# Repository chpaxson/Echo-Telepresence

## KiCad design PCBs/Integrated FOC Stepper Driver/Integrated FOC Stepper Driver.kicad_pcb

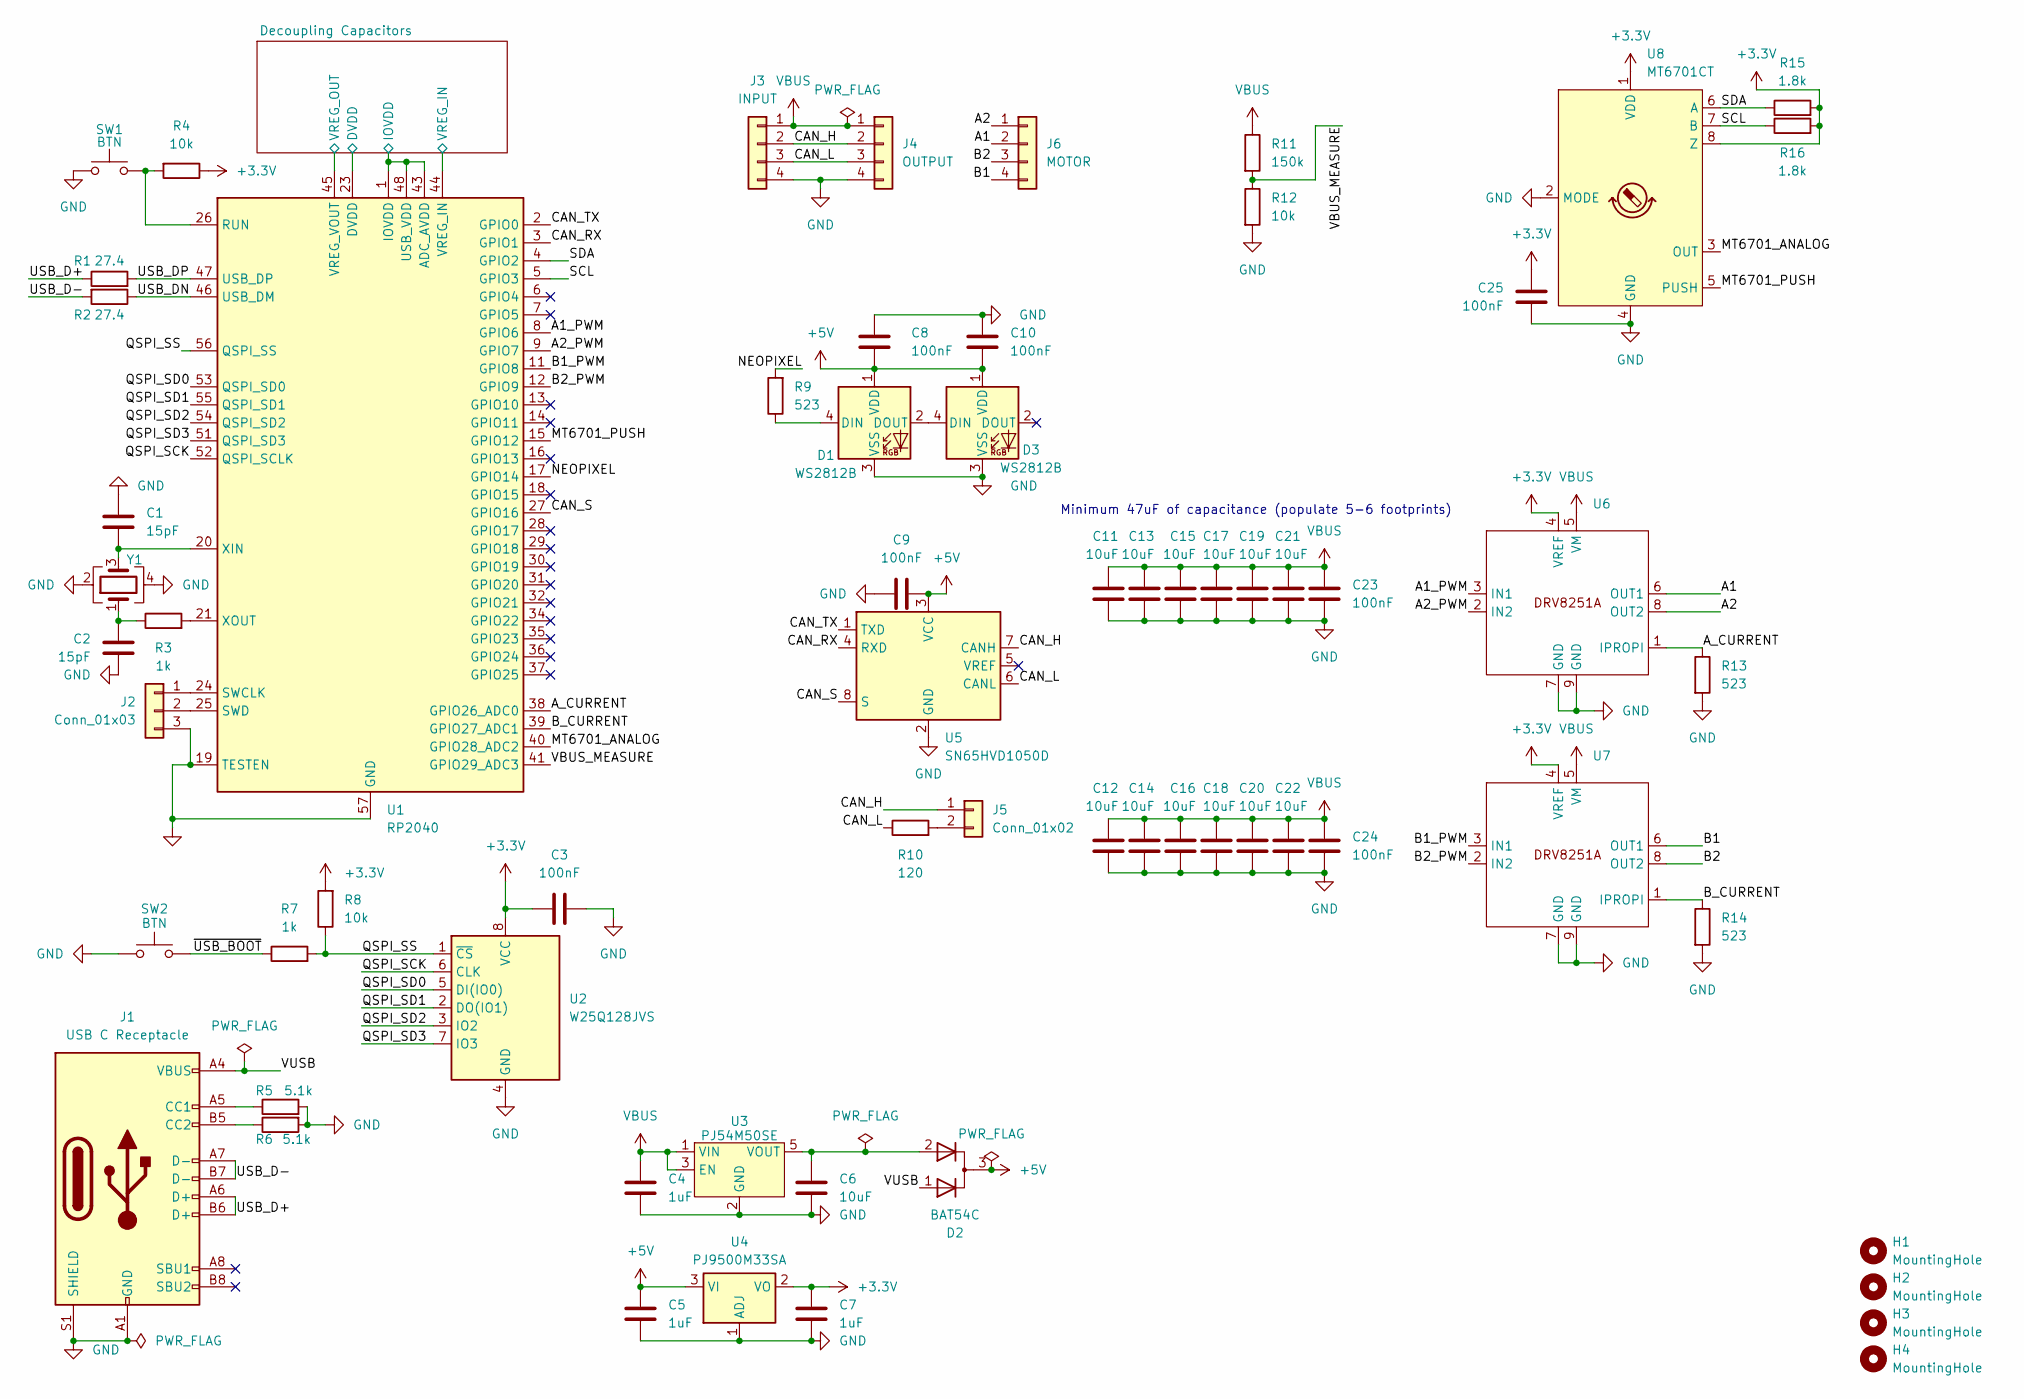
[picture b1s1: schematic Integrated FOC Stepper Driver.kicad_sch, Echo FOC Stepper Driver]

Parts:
C1, C2: 15pF; C_0402_1005Metric; LCSC C18164617
C3, C8, C9, C10, C23, C24: 100nF; C_0402_1005Metric; LCSC C960916
C4, C5, C7: 1uF; C_0402_1005Metric; LCSC C1518208
C6: 10uF; C_0603_1608Metric; LCSC C96446
C11, C12, C13, C14, C15, C16, C17, C18, C19, C20, C21, C22: 10uF; C_0805_2012Metric; LCSC C440198
C25: 100nF; C_0603_1608Metric; LCSC C1591
D1, D3: WS2812B; LED_WS2812B_PLCC4_5.0x5.0mm_P3.2mm
D2: BAT54C; SOT-23; LCSC C37704
H1, H2, H3, H4: MountingHole; MountingHole_3.2mm_M3_DIN965_Pad
J1: USB C Receptacle; USB_C_Receptacle_G-Switch_GT-USB-7010ASV; LCSC C2988369
J2: Conn_01x03; PinHeader_1x03_P2.54mm_Vertical
J3: INPUT; JST_PH_S4B-PH-K_1x04_P2.00mm_Horizontal; LCSC C157926
J4: OUTPUT; JST_PH_S4B-PH-K_1x04_P2.00mm_Horizontal; LCSC C157926
J5: Conn_01x02; PinHeader_1x02_P2.54mm_Vertical
J6: MOTOR; JST_XH_S4B-XH-A_1x04_P2.50mm_Horizontal; LCSC C157925
R1, R2: 27.4; R_0402_1005Metric; LCSC C274349
R3, R7: 1k; R_0402_1005Metric; LCSC C105637
R4, R8, R12: 10k; R_0402_1005Metric; LCSC C60490
R5, R6: 5.1k; R_0402_1005Metric; LCSC C105872
R9, R13, R14: 523; R_0402_1005Metric; LCSC C517803
R10: 120; R_0402_1005Metric; LCSC C114758
R11: 150k; R_0402_1005Metric; LCSC C93947
R15, R16: 1.8k; R_0402_1005Metric; LCSC C163481
SW1, SW2: BTN; SW_SPST_B3U-1000P; LCSC C231329
U1: RP2040; QFN-56-1EP_7x7mm_P0.4mm_EP3.2x3.2mm; LCSC C2040
U2: W25Q128JVS; SOIC-8_5.23x5.23mm_P1.27mm; LCSC C97521
U3: PJ54M50SE; SOT-23-5; LCSC C41784039
U4: PJ9500M33SA; SOT-23; LCSC C20618178
U5: SN65HVD1050D; SOIC-8_3.9x4.9mm_P1.27mm; LCSC C14019
U6, U7: Texas_HSOP-8-1EP_3.9x4.9mm_P1.27mm_ThermalVias; LCSC C5218844
U8: MT6701CT; SO-8_3.9x4.9mm_P1.27mm; LCSC C19711153
Y1: ABM8-272-T3; Crystal_SMD_3225-4Pin_3.2x2.5mm; LCSC C20625731

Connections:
+1V1: U1.23 (DVDD), U1.45 (VREG_VOUT), U1.50 (DVDD); also elsewhere on the board
+3.3V: C3.1, C7.1, C25.1, R4.1, R8.2, R15.2, R16.2, U1.1 (IOVDD), U1.10 (IOVDD), U1.22 (IOVDD), U1.33 (IOVDD), U1.42 (IOVDD), U1.43 (ADC_AVDD), U1.44 (VREG_IN), U1.48 (USB_VDD), U1.49 (IOVDD), U2.8 (VCC), U4.2 (VO), U6.4 (VREF), U7.4 (VREF), U8.1 (VDD), U8.8 (Z); also elsewhere on the board
+5V: C5.1, C8.1, C9.1, C10.1, D1.1 (VDD), D2.3 (K), D3.1 (VDD), U4.3 (VI), U5.3 (VCC)
/A1: J6.2, U6.6 (OUT1)
/A1_PWM: U1.8 (GPIO6), U6.3 (IN1)
/A2: J6.1, U6.8 (OUT2)
/A2_PWM: U1.9 (GPIO7), U6.2 (IN2)
/A_CURRENT: R13.1, U1.38 (GPIO26_ADC0), U6.1 (IPROPI)
/B1: J6.4, U7.6 (OUT1)
/B1_PWM: U1.11 (GPIO8), U7.3 (IN1)
/B2: J6.3, U7.8 (OUT2)
/B2_PWM: U1.12 (GPIO9), U7.2 (IN2)
/B_CURRENT: R14.1, U1.39 (GPIO27_ADC1), U7.1 (IPROPI)
/CAN_H: J3.2, J4.2, J5.1, U5.7 (CANH)
/CAN_L: J3.3, J4.3, R10.1, U5.6 (CANL)
/CAN_RX: U1.3 (GPIO1), U5.4 (RXD)
/CAN_S: U1.27 (GPIO16), U5.8 (S)
/CAN_TX: U1.2 (GPIO0), U5.1 (TXD)
/MT6701_ANALOG: U1.40 (GPIO28_ADC2), U8.3 (OUT)
/MT6701_PUSH: U1.15 (GPIO12), U8.5 (PUSH)
/NEOPIXEL: R9.2, U1.17 (GPIO14)
/QSPI_SCK: U1.52 (QSPI_SCLK), U2.6 (CLK)
/QSPI_SD0: U1.53 (QSPI_SD0), U2.5 (DI(IO0))
/QSPI_SD1: U1.55 (QSPI_SD1), U2.2 (DO(IO1))
/QSPI_SD2: U1.54 (QSPI_SD2), U2.3 (IO2)
/QSPI_SD3: U1.51 (QSPI_SD3), U2.7 (IO3)
/QSPI_SS: R7.2, R8.1, U1.56 (QSPI_SS), U2.1 (~CS)
/SCL: R16.1, U1.5 (GPIO3), U8.7 (B)
/SDA: R15.1, U1.4 (GPIO2), U8.6 (A)
/USB_D+: J1.A6 (D+), J1.B6 (D+), R1.1
/USB_D-: J1.A7 (D-), J1.B7 (D-), R2.2
/USB_DN: R2.1, U1.46 (USB_DM)
/USB_DP: R1.2, U1.47 (USB_DP)
/VBUS_MEASURE: R11.2, R12.1, U1.41 (GPIO29_ADC3)
/VUSB: D2.1 (A), J1.A4 (VBUS), J1.A9 (VBUS), J1.B4 (VBUS), J1.B9 (VBUS)
/~USB_BOOT: R7.1, SW2.2
GND: C1.2, C2.1, C3.2, C4.2, C5.2, C6.2, C7.2, C8.2, C9.2, C10.2, C11.2, C12.2, C13.2, C14.2, C15.2, C16.2, C17.2, C18.2, C19.2, C20.2, C21.2, C22.2, C23.2, C24.2, C25.2, D1.3 (VSS), D3.3 (VSS), J1.A1 (GND), J1.A12 (GND), J1.B1 (GND), J1.B12 (GND), J1.S1 (SHIELD), J2.3, J3.4, J4.4, R5.2, R6.2, R12.2, R13.2, R14.2, SW1.2, SW2.1, U1.19 (TESTEN), U1.57 (GND), U2.4 (GND), U3.2 (GND), U4.1 (ADJ), U5.2 (GND), U6.7 (GND), U6.9 (GND), U7.7 (GND), U7.9 (GND), U8.2 (MODE), U8.4 (GND), Y1.2, Y1.4; also elsewhere on the board
unnamed: C2.2, R3.1, Y1.1
unnamed: D1.4 (DIN), R9.1
unnamed: D1.2 (DOUT), D3.4 (DIN)
unnamed: J1.A5 (CC1), R5.1
unnamed: J1.B5 (CC2), R6.1
unnamed: J2.1, U1.24 (SWCLK)
unnamed: J2.2, U1.25 (SWD)
unnamed: J5.2, R10.2
unnamed: R4.2, SW1.1, U1.26 (RUN)
unnamed: C1.1, U1.20 (XIN), Y1.3
unnamed: R3.2, U1.21 (XOUT)
unnamed: C6.1, D2.2 (A), U3.5 (VOUT)
VBUS: C4.1, C11.1, C12.1, C13.1, C14.1, C15.1, C16.1, C17.1, C18.1, C19.1, C20.1, C21.1, C22.1, C23.1, C24.1, J3.1, J4.1, R11.1, U3.1 (VIN), U3.3 (EN), U6.5 (VM), U7.5 (VM)

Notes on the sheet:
Minimum 47uF of capacitance (populate 5-6 footprints)

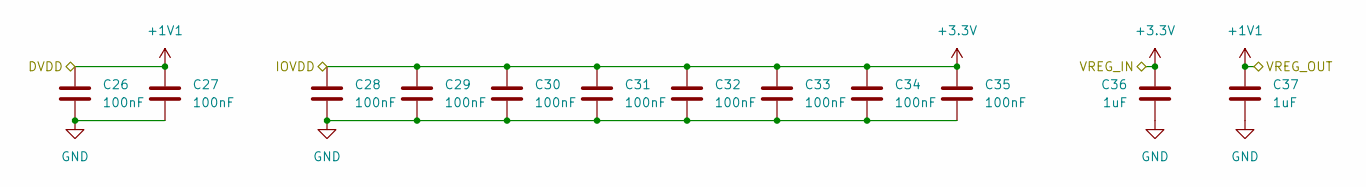
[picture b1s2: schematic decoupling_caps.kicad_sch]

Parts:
C26, C27, C28, C29, C30, C31, C32, C33, C34, C35: 100nF; C_0402_1005Metric; LCSC C960916
C36, C37: 1uF; C_0402_1005Metric; LCSC C1518208

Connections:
+1V1: C26.1, C27.1, C37.1; also elsewhere on the board
+3.3V: C28.1, C29.1, C30.1, C31.1, C32.1, C33.1, C34.1, C35.1, C36.1; also elsewhere on the board
GND: C26.2, C27.2, C28.2, C29.2, C30.2, C31.2, C32.2, C33.2, C34.2, C35.2, C36.2, C37.2; also elsewhere on the board

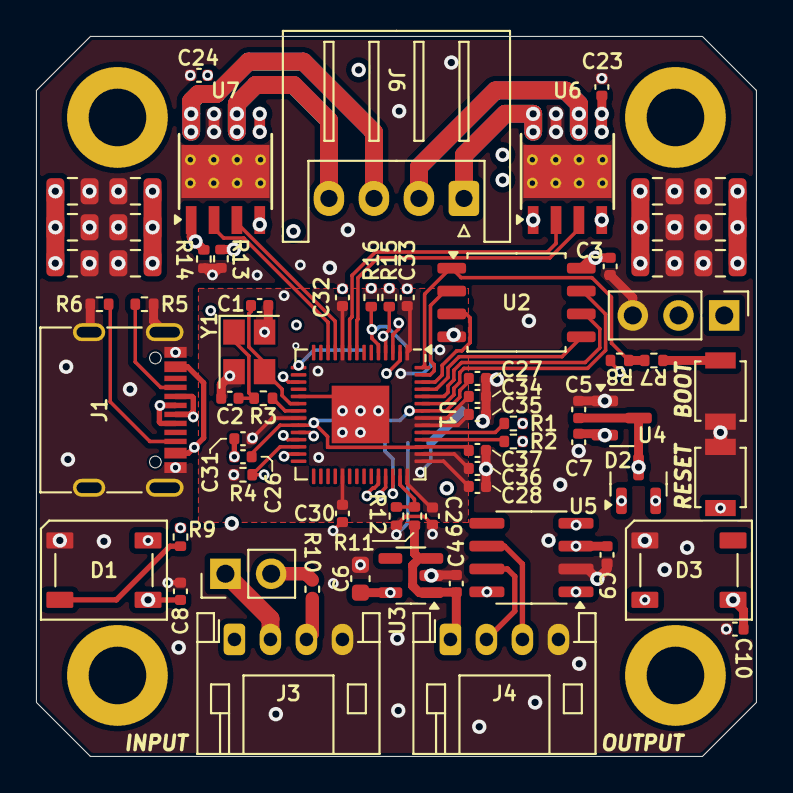
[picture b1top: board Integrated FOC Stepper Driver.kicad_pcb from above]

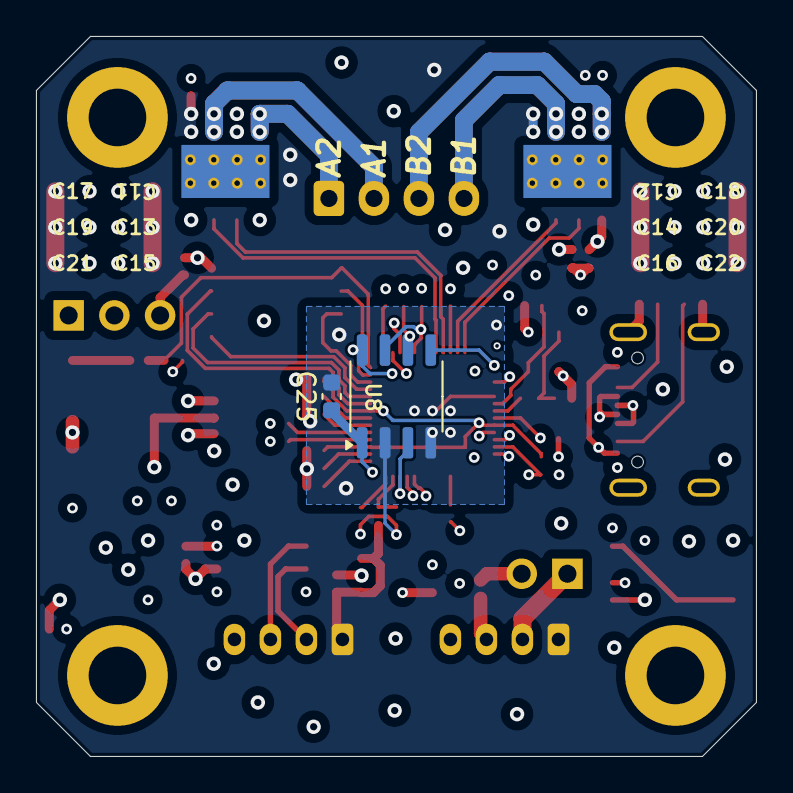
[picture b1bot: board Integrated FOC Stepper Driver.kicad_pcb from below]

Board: 6 copper layers, 40.0 x 40.0 mm, 77 parts (2 on the bottom side), 50 nets.

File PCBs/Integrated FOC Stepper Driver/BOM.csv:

"C1, C2",15pF,~,Capacitor_SMD:C_0402_1005Metric,2,C18164617
"C3, C8-C10, C23, C24, C26-C35",100nF,~,Capacitor_SMD:C_0402_1005Metric,16,C960916
"C4, C5, C7, C36, C37",1uF,~,Capacitor_SMD:C_0402_1005Metric,5,C1518208
C6,10uF,~,Capacitor_SMD:C_0603_1608Metric,1,C96446
C11-C22,10uF,~,Capacitor_SMD:C_0805_2012Metric,12,C440198
C25,100nF,~,Capacitor_SMD:C_0603_1608Metric,1,C1591
D2,BAT54C,~,Package_TO_SOT_SMD:SOT-23,1,C37704
J1,USB C Receptacle,https://www.usb.org/sites/default/files/documents/usb_type-c.zip,Connector_USB:USB_C_Receptacle_G-Switch_GT-USB-7010ASV,1,C2988369
J3,INPUT,~,Connector_JST:JST_PH_S4B-PH-K_1x04_P2.00mm_Horizontal,1,C157926
J4,OUTPUT,~,Connector_JST:JST_PH_S4B-PH-K_1x04_P2.00mm_Horizontal,1,C157926
J6,MOTOR,~,Connector_JST:JST_XH_S4B-XH-A_1x04_P2.50mm_Horizontal,1,C157925
"R1, R2",27.4,~,Resistor_SMD:R_0402_1005Metric,2,C274349
"R3, R7",1k,~,Resistor_SMD:R_0402_1005Metric,2,C105637
"R4, R8, R12",10k,~,Resistor_SMD:R_0402_1005Metric,3,C60490
"R5, R6",5.1k,~,Resistor_SMD:R_0402_1005Metric,2,C105872
"R9, R13, R14",523,~,Resistor_SMD:R_0402_1005Metric,3,C517803
R10,120,~,Resistor_SMD:R_0402_1005Metric,1,C114758
R11,150k,~,Resistor_SMD:R_0402_1005Metric,1,C93947
"R15, R16",1.8k,~,Resistor_SMD:R_0402_1005Metric,2,C163481
"SW1, SW2",BTN,~,Button_Switch_SMD:SW_SPST_B3U-1000P,2,C231329
U1,RP2040,https://datasheets.raspberrypi.com/rp2040/rp2040-datasheet.pdf,Package_DFN_QFN:QFN-56-1EP_7x7mm_P0.4mm_EP3.2x3.2mm,1,C2040
U2,W25Q128JVS,https://www.winbond.com/resource-files/w25q128jv_dtr%20revc%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,Package_SO:SOIC-8_5.23x5.23mm_P1.27mm,1,C97521
U3,PJ54M50SE,,Package_TO_SOT_SMD:SOT-23-5,1,C41784039
U4,PJ9500M33SA,,Package_TO_SOT_SMD:SOT-23,1,C20618178
U5,SN65HVD1050D,http://www.ti.com/lit/ds/symlink/sn65hvd1050.pdf,Package_SO:SOIC-8_3.9x4.9mm_P1.27mm,1,C14019
"U6, U7",~,,Package_SO:Texas_HSOP-8-1EP_3.9x4.9mm_P1.27mm_ThermalVias,2,C5218844
U8,MT6701CT,https://www.magntek.com.cn/upload/MT6701_Rev.1.5.pdf,Package_SO:SO-8_3.9x4.9mm_P1.27mm,1,C19711153
Y1,ABM8-272-T3,~,Crystal:Crystal_SMD_3225-4Pin_3.2x2.5mm,1,C20625731

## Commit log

2025-02-01 PCB Project File Initialization
2025-02-01 Create symbol+footprint libraries for DRV8301, begin refining DRV8301 symbol
2025-02-01 Finish DRV8301 symbol, start implementing circuitry around it
2025-02-03 Add AMS1117 LDO to give 3.3V power to MCU
2025-02-04 Switching to Stepper driver with half bridges
2025-02-06 Add velocity testing sketch
2025-02-11 Hopefully finally chose a motor driver
2025-02-12 Start working on an integrated stepper driver
2025-02-14 Rearrange schematic, start adding CAN bus hardware
2025-02-14 Set up LDOs
2025-02-14 Start layout
2025-02-17 V1 of driver PCB
2025-02-17 Update trace clearance
2025-02-17 Clean up schematic, remove all 0.4/0.2mm vias from layout
2025-02-17 Remove all 0.6/0.3mm vias and add HV keep-out zone around MCU
2025-02-18 Remove extra motor.kicad_sch file
2025-02-18 Layout V2
    Added a voltage divider from VBUS to measure up to 48V on ADC
    Switch motor connector to JST-XH at 3A instead of 2A
    Relayout to accomodate changes
2025-02-19 Start RP2350 design
2025-02-19 Start re-layout with advice from John
    6-layer stackup:
    - Power
    - Ground
    - Signal
    - Signal
    - Ground
2025-02-20 Finish new layout
2025-02-20 Small updates to layout
2025-02-20 Switch to 0805 capacitors instead of stacked 2220 capacitors
2025-02-20 Update bypass capacitors
2025-02-20 (did not ctrl+s sorry)
2025-02-21 Generate new Gerbers
2025-02-21 Update gerber export zip
2025-02-21 Make little helical gear test - does not work
2025-02-22 Fix a single damn via that was too small
2025-02-23 Update gerbers
2025-02-23 Start motor controller firmware
2025-03-13 Motor controller case V1 design
2025-03-13 Generate interactive BOM for motor driver PCB
2025-03-14 Set up RP2040 motor controller firmware project
2025-03-19 Make magnet alignment jig
2025-04-03 Start trying to add stepper-pico library for testing
2025-04-04 Try to set up I2C communication
    Doesn't appear to work - I think it has something to do with the read function
2025-04-07 new firmware
2025-04-07 Add stencil DXF and quick magnetic angle sensor test Arduino sketch
2025-04-08 i2c scan and i2c testing functioiality
2025-04-08 Set up host robot controller Espressif-IDF project
2025-04-08 migrated i2c scan and i2c read to lib
2025-04-09 i2c functionality finalized and i2c scan fixed
2025-04-10 added basic stepper functionality
2025-04-11 Briefly implement multicore
2025-04-11 Get simultaneous current, VBUS, and encoder measurement working with moving motor
2025-04-17 Create Web GUI in Vue, implement basic visualization and control
2025-04-17 Slight cleaning
2025-04-17 Start working on ESP32 web server
2025-04-18 Renaming robot controller project
2025-04-18 Start developing more refined version of GUI with multiple pages
2025-04-19 Get dragging working on visualization
2025-04-19 Add slider elements and a drawing canvas
2025-04-20 starting can implmentation
2025-04-23 rolled change, currently working with no can functionailty
2025-04-23 CAN functionality compiles, cleaned up main
2025-04-24 Move GUI files into robot_controller project
2025-04-24 CAN funcationality tested with probe
2025-04-24 can-testing
    CAN-Testing
2025-04-25 Figuring out some bugs in the GUI and moving files around
2025-04-26 CAN Setup up ESP32
2025-04-27 Update RP2040 CAN code slightly for testing
2025-04-28 Finish workspace projection for visualization
2025-04-28 Get ESP32->RP2040 CAN communication working
2025-04-28 Refactor robot_controller
2025-04-28 Update gitignore
2025-04-29 implemented common files within arduino-foc into pico-sdk
2025-04-29 Remove vestigial file in motorcontroller firmware folder for GUI
2025-04-29 implementated Sensor class from Arduino FOC
2025-04-30 UNTESTED! Implemented the 4PWM Stepper Driver from Simple FOC
2025-04-30 refactored to match simple foc file management
2025-05-01 implemented Stepper Motor from Arudino FOC, UNTESTED
2025-05-01 OPEN LOOP WORKS
2025-05-01 added InlineCurrentSensing
2025-05-01 Add sw CAD files
2025-05-01 Remove build folders
2025-05-02 Refactor again
2025-05-02 Restart robot_controller workspace
2025-05-02 REST communication between GUI and ESP32 :)
2025-05-02 Closed Loop works with no Current Sensing
2025-05-02 Add starting files for robot controller/PSU box
2025-05-06 Controller PSU Box
2025-05-06 Move PCBs to Hardware folder
2025-05-07 Yet more reformatting, Web GUI work
2025-05-07 Pushing before nuking to restart with TailwindCSS
2025-05-07 Basic implementation based on Sakai PrimeVue template
2025-05-07 Start setting up detailed views
2025-05-08 Bit of work on the GUI, prepping to set up WebSocket comms
2025-05-08 Back to functioning REST server with new ESP32 project
2025-05-08 Bidirectional websocket communication works, starting to add features to toggle whether the visualization is driven by the UI or by the robot/potentiometers
2025-05-08 A bit of front end work to set up robot linking
2025-05-09 Charles - pushing to edit on my computer a bit
2025-05-09 very bad haptic controll
2025-05-09 Update, start upping baud rate to great success :)
2025-05-09 Trying to integrate web gui and robot controller
2025-05-09 Some further work integrating GUI and robot controller
2025-05-09 Update some small things
2025-05-10 Presentation State
2025-05-10 Push right before presentation
